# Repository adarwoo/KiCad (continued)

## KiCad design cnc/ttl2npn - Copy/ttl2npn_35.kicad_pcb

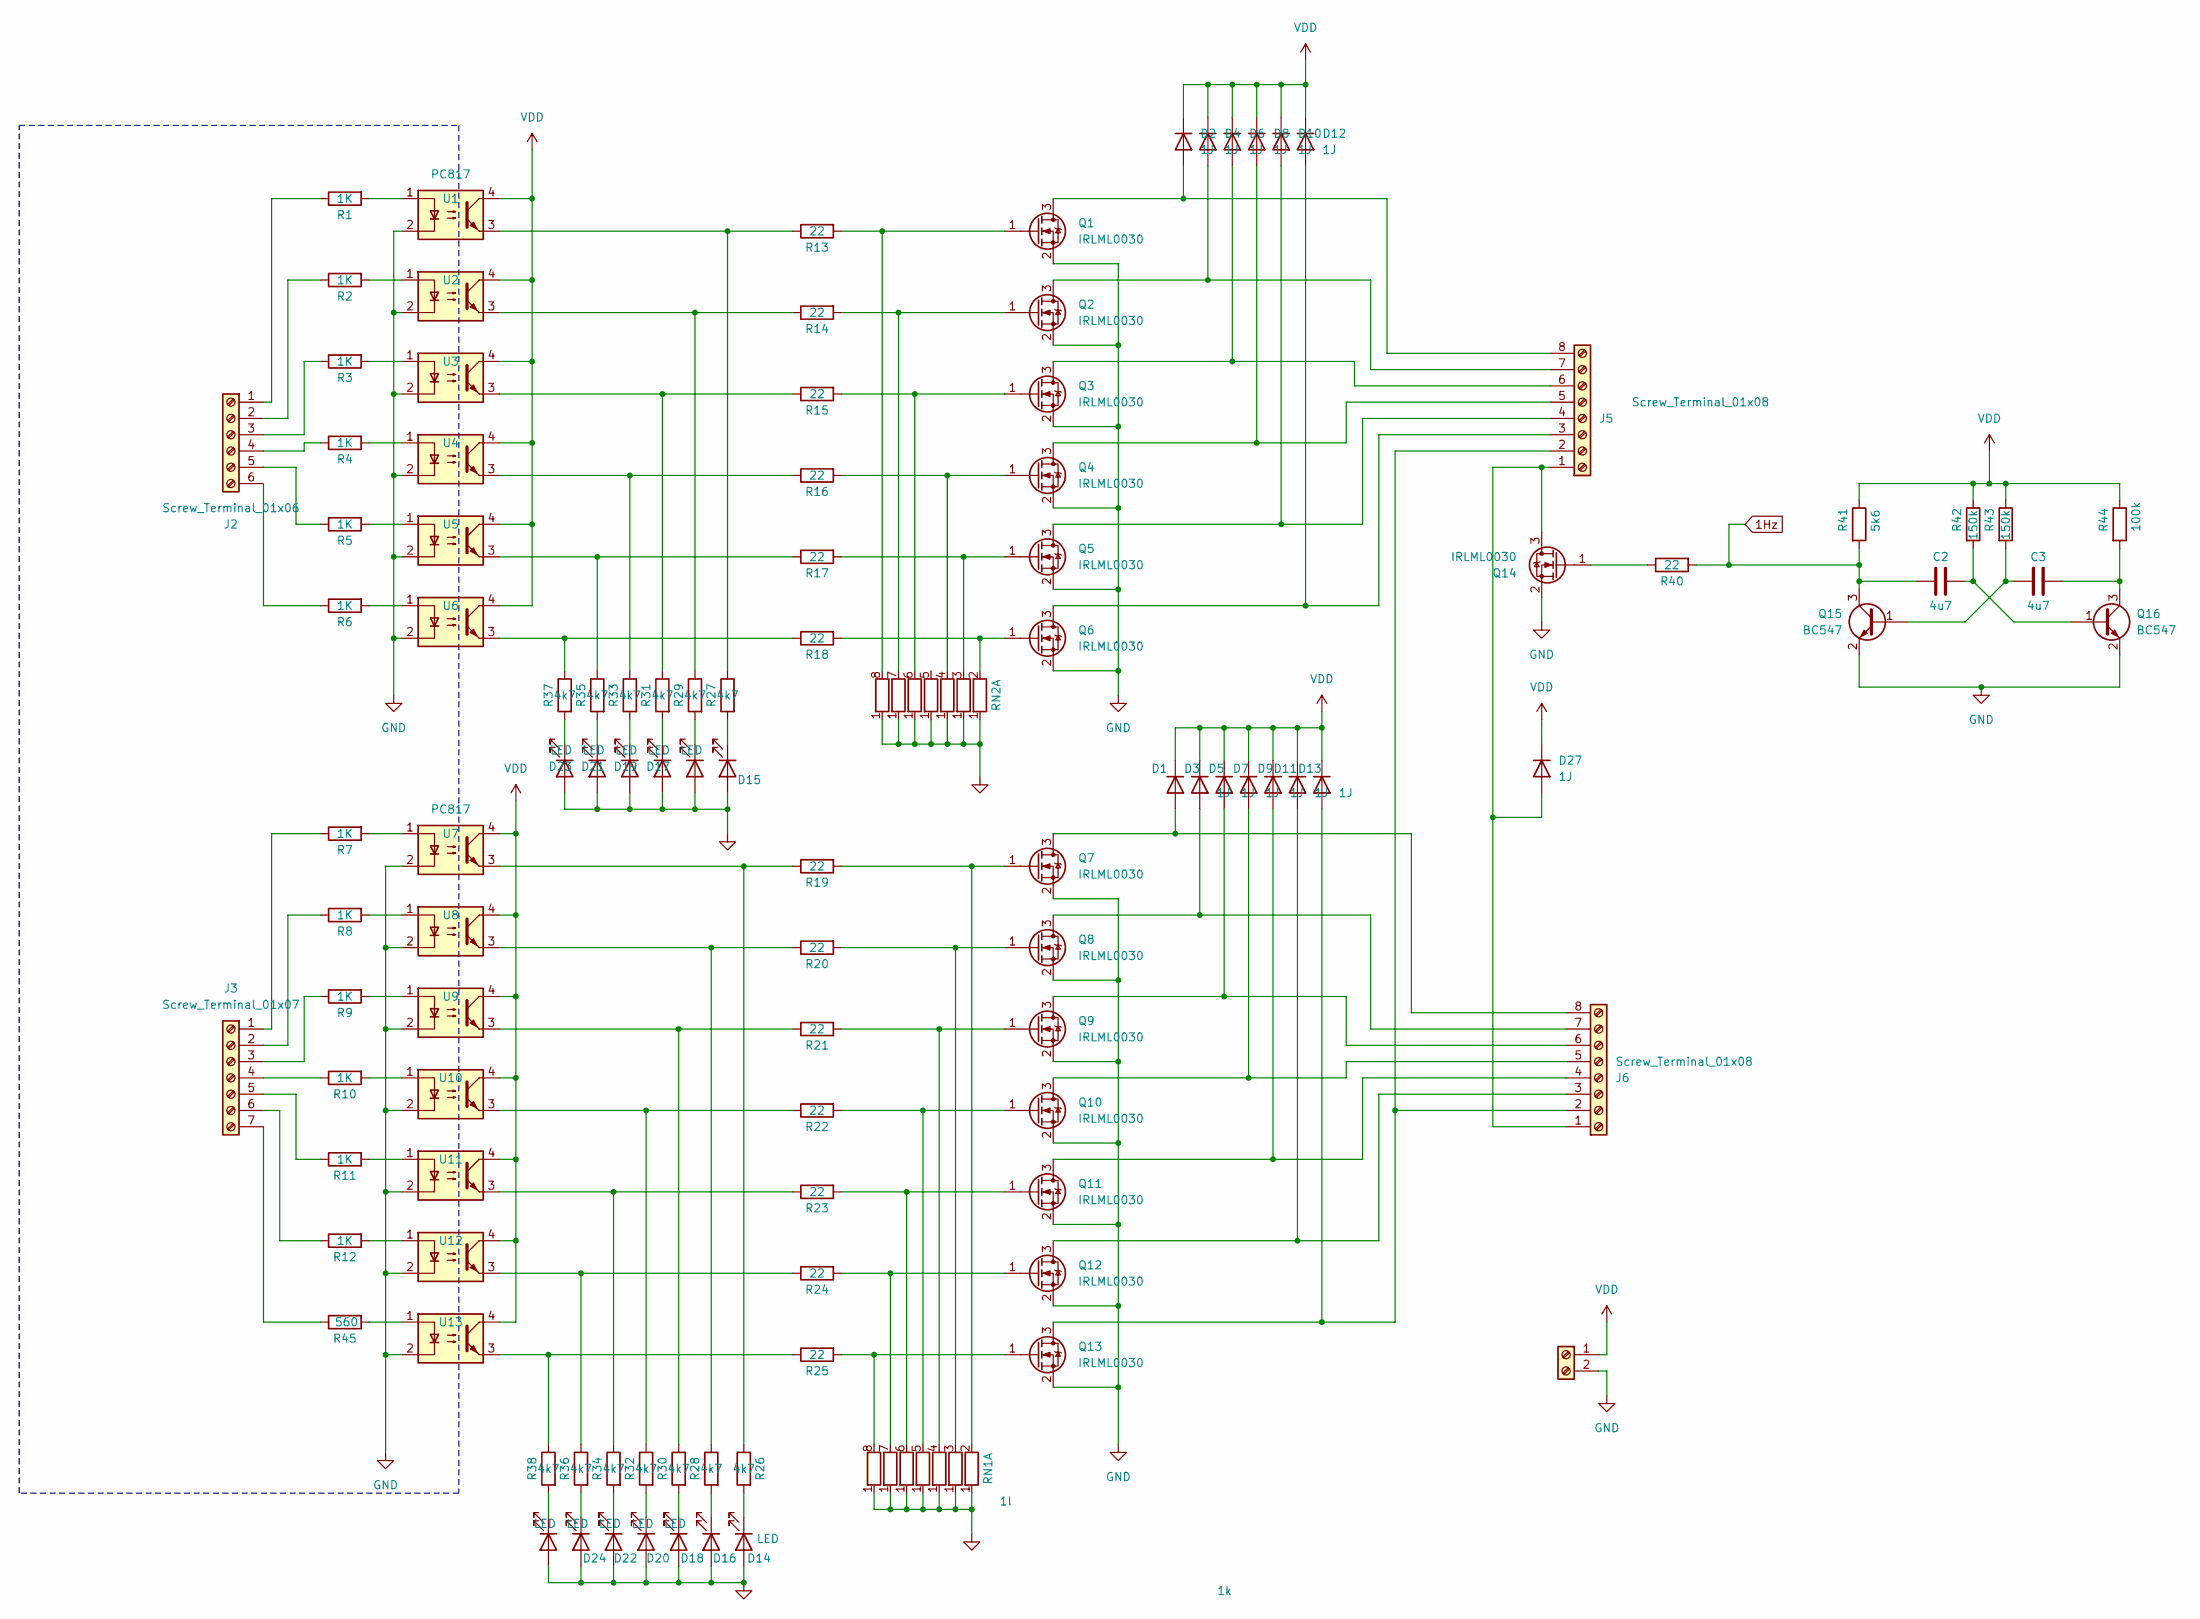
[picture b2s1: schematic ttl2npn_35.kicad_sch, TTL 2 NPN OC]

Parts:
C2, C3: 4u7; C_1206_3216Metric
D1, D2, D3, D4, D5, D6, D7, D8, D9, D10, D11, D12, D13, D27: 1J; D_MicroSMP_AK
D14, D15, D16, D17, D18, D19, D20, D21, D22, D23, D24, D25, D26: LED; LED_D3.0mm
J2: Screw_Terminal_01x06; PhoenixContact_MCV_1,5_6-G-3.81_1x06_P3.81mm_Vertical
J3: Screw_Terminal_01x07; PhoenixContact_MCV_1,5_7-G-3.81_1x07_P3.81mm_Vertical
J4: Screw_Terminal_01x02; PhoenixContact_MCV_1,5_2-G-3.81_1x02_P3.81mm_Vertical
J5, J6: Screw_Terminal_01x08; PhoenixContact_MCV_1,5_8-G-3.81_1x08_P3.81mm_Vertical
Q1, Q2, Q3, Q4, Q5, Q6, Q7, Q8, Q9, Q10, Q11, Q12, Q13, Q14: IRLML0030; SOT-23
Q15, Q16: BC547; SOT-23
R1, R2, R3, R4, R5, R6, R7, R8, R9, R10, R11, R12: 1K; R_0805_2012Metric
R13, R14, R15, R16, R17, R18, R19, R20, R21, R22, R23, R24, R25, R40: 22; R_0805_2012Metric
R26, R27, R28, R29, R30, R31, R32, R33, R34, R35, R36, R37, R38: 4k7; R_0805_2012Metric
R41: 5k6; R_0805_2012Metric
R42, R43: 150k; R_0805_2012Metric
R44: 100k; R_0805_2012Metric
R45: 560; R_0805_2012Metric
RN1: 1l; R_Array_SIP8
RN2: 1k; R_Array_SIP8
U1, U2, U3, U4, U5, U6, U7, U8, U9, U10, U11, U12, U13: PC817; DIP-4_W7.62mm

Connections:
1Hz: C2.1, Q15.3 (C), R40.2, R41.2
GND: D14.2 (A), D15.2 (A), D16.2 (A), D17.2 (A), D18.2 (A), D19.2 (A), D20.2 (A), D21.2 (A), D22.2 (A), D23.2 (A), D24.2 (A), D25.2 (A), D26.2 (A), J4.2, Q1.2 (S), Q2.2 (S), Q3.2 (S), Q4.2 (S), Q5.2 (S), Q6.2 (S), Q7.2 (S), Q8.2 (S), Q9.2 (S), Q10.2 (S), Q11.2 (S), Q12.2 (S), Q13.2 (S), Q14.2 (S), Q15.2 (E), Q16.2 (E), RN1.1 (R1), RN2.1 (R1), U1.2, U2.2, U3.2, U4.2, U5.2, U6.2, U7.2, U8.2, U9.2, U10.2, U11.2, U12.2, U13.2
unnamed: D1.2 (A), J6.8, Q7.3 (D)
unnamed: D2.2 (A), J5.8, Q1.3 (D)
unnamed: D3.2 (A), J6.7, Q8.3 (D)
unnamed: D4.2 (A), J5.7, Q2.3 (D)
unnamed: D5.2 (A), J6.6, Q9.3 (D)
unnamed: D6.2 (A), J5.6, Q3.3 (D)
unnamed: D7.2 (A), J6.5, Q10.3 (D)
unnamed: D8.2 (A), J5.5, Q4.3 (D)
unnamed: D9.2 (A), J6.4, Q11.3 (D)
unnamed: D10.2 (A), J5.4, Q5.3 (D)
unnamed: D11.2 (A), J6.3, Q12.3 (D)
unnamed: D12.2 (A), J5.3, Q6.3 (D)
unnamed: D13.2 (A), J5.2, J6.2, Q13.3 (D)
unnamed: D14.1 (K), R26.2
unnamed: D15.1 (K), R27.2
unnamed: D16.1 (K), R28.2
unnamed: D17.1 (K), R29.2
unnamed: D18.1 (K), R30.2
unnamed: D19.1 (K), R31.2
unnamed: D20.1 (K), R32.2
unnamed: D21.1 (K), R33.2
unnamed: D22.1 (K), R34.2
unnamed: D23.1 (K), R35.2
unnamed: D24.1 (K), R36.2
unnamed: D25.1 (K), R37.2
unnamed: D26.1 (K), R38.2
unnamed: D27.2 (A), J5.1, J6.1, Q14.3 (D)
unnamed: J2.1, R1.1
unnamed: J2.2, R2.1
unnamed: J2.3, R3.1
unnamed: J2.4, R4.1
unnamed: J2.5, R5.1
unnamed: J2.6, R6.1
unnamed: J3.1, R7.1
unnamed: J3.2, R8.1
unnamed: J3.3, R9.1
unnamed: J3.4, R10.1
unnamed: J3.5, R11.1
unnamed: J3.6, R12.1
unnamed: J3.7, R45.1
unnamed: Q1.1 (G), R13.2, RN2.8 (R7.2)
unnamed: Q2.1 (G), R14.2, RN2.7 (R6.2)
unnamed: Q3.1 (G), R15.2, RN2.6 (R5.2)
unnamed: Q4.1 (G), R16.2, RN2.4 (R3.2)
unnamed: Q5.1 (G), R17.2, RN2.3 (R2.2)
unnamed: Q6.1 (G), R18.2, RN2.2 (R1.2)
unnamed: Q7.1 (G), R19.2, RN1.2 (R1.2)
unnamed: Q8.1 (G), R20.2, RN1.3 (R2.2)
unnamed: Q9.1 (G), R21.2, RN1.4 (R3.2)
unnamed: Q10.1 (G), R22.2, RN1.5 (R4.2)
unnamed: Q11.1 (G), R23.2, RN1.6 (R5.2)
unnamed: Q12.1 (G), R24.2, RN1.7 (R6.2)
unnamed: Q13.1 (G), R25.2, RN1.8 (R7.2)
unnamed: Q14.1 (G), R40.1
unnamed: C3.1, Q15.1 (B), R43.2
unnamed: C2.2, Q16.1 (B), R42.2
unnamed: C3.2, Q16.3 (C), R44.2
unnamed: R1.2, U1.1
unnamed: R2.2, U2.1
unnamed: R3.2, U3.1
unnamed: R4.2, U4.1
unnamed: R5.2, U5.1
unnamed: R6.2, U6.1
unnamed: R7.2, U7.1
unnamed: R8.2, U8.1
unnamed: R9.2, U9.1
unnamed: R10.2, U10.1
unnamed: R11.2, U11.1
unnamed: R12.2, U12.1
unnamed: R13.1, R27.1, U1.3
unnamed: R14.1, R29.1, U2.3
unnamed: R15.1, R31.1, U3.3
unnamed: R16.1, R33.1, U4.3
unnamed: R17.1, R35.1, U5.3
unnamed: R18.1, R37.1, U6.3
unnamed: R19.1, R26.1, U7.3
unnamed: R20.1, R28.1, U8.3
unnamed: R21.1, R30.1, U9.3
unnamed: R22.1, R32.1, U10.3
unnamed: R23.1, R34.1, U11.3
unnamed: R24.1, R36.1, U12.3
unnamed: R25.1, R38.1, U13.3
unnamed: R45.2, U13.1
VDD: D1.1 (K), D2.1 (K), D3.1 (K), D4.1 (K), D5.1 (K), D6.1 (K), D7.1 (K), D8.1 (K), D9.1 (K), D10.1 (K), D11.1 (K), D12.1 (K), D13.1 (K), D27.1 (K), J4.1, R41.1, R42.1, R43.1, R44.1, U1.4, U2.4, U3.4, U4.4, U5.4, U6.4, U7.4, U8.4, U9.4, U10.4, U11.4, U12.4, U13.4

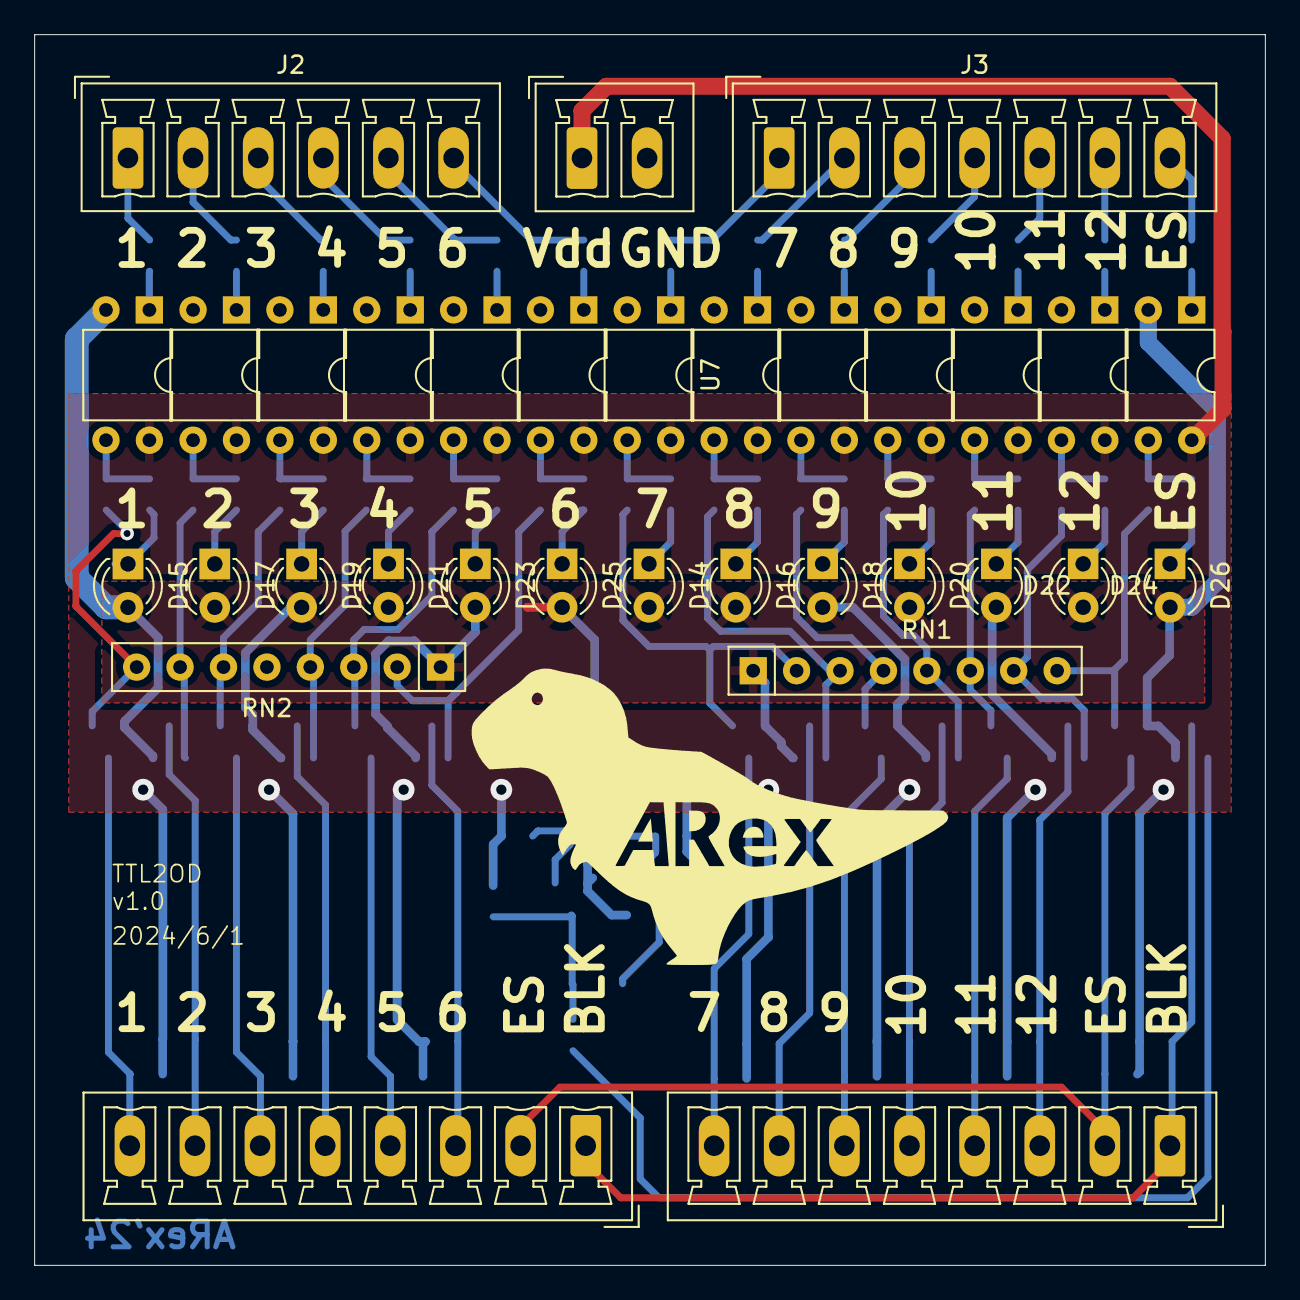
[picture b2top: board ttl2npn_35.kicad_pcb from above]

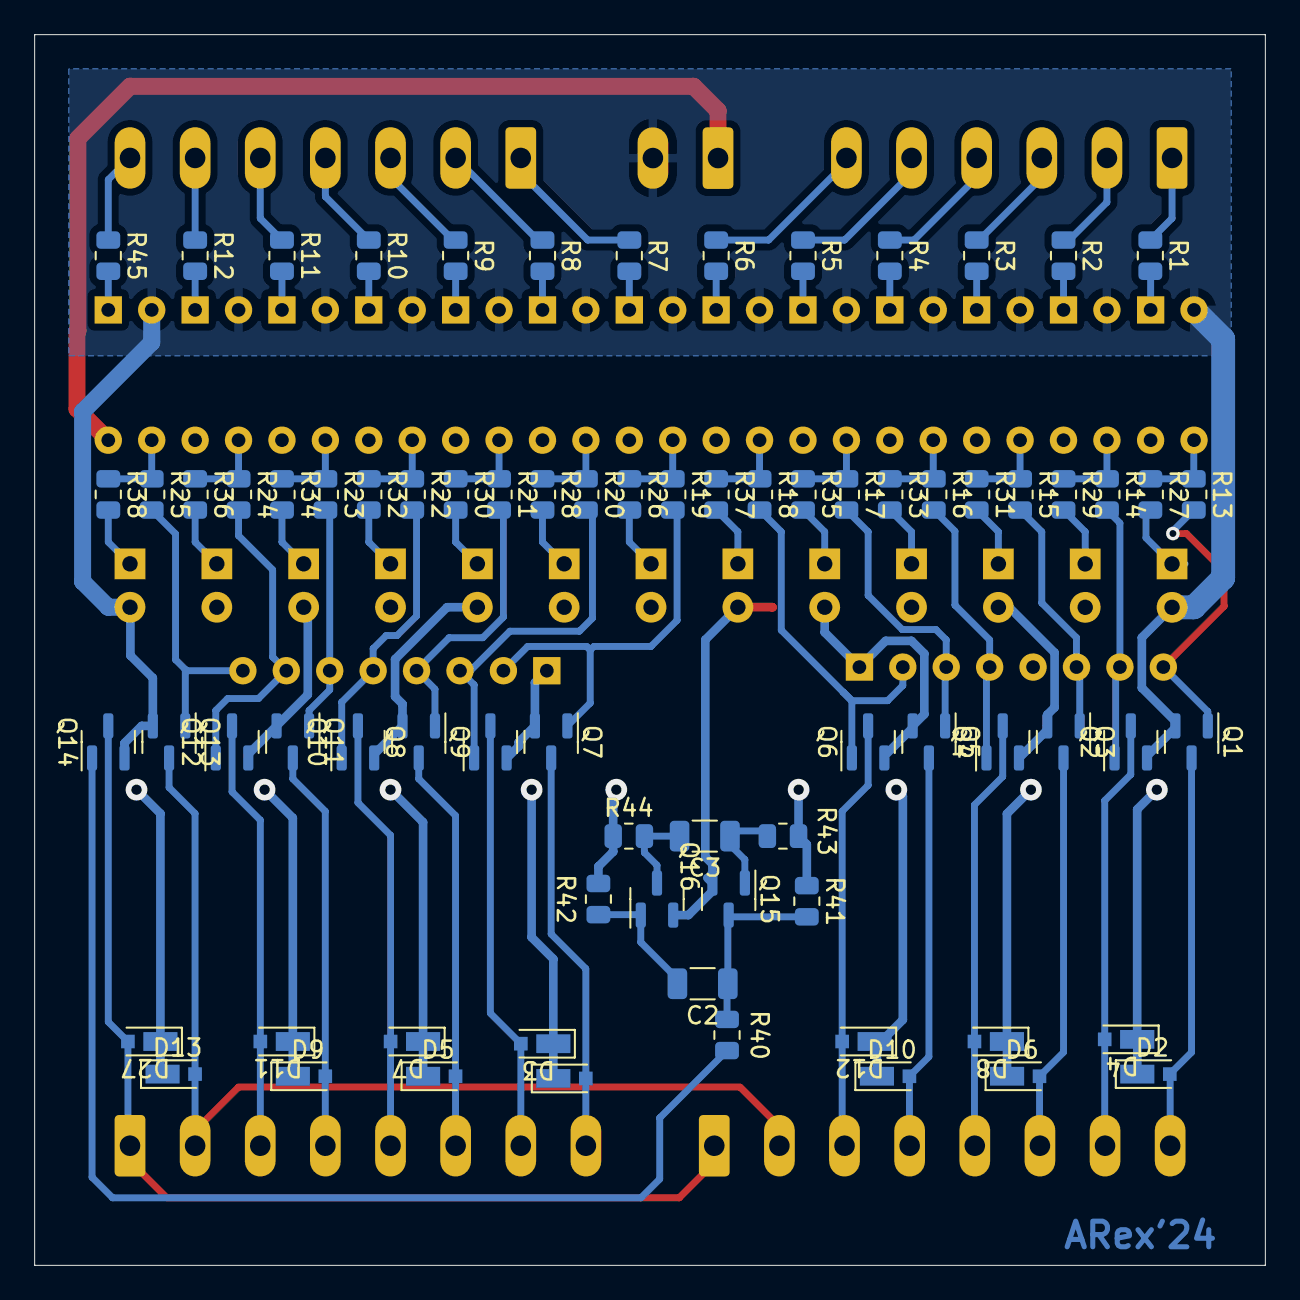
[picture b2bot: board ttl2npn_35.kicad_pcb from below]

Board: 2 copper layers, 72.0 x 72.0 mm, 109 parts (76 on the bottom side), 86 nets.

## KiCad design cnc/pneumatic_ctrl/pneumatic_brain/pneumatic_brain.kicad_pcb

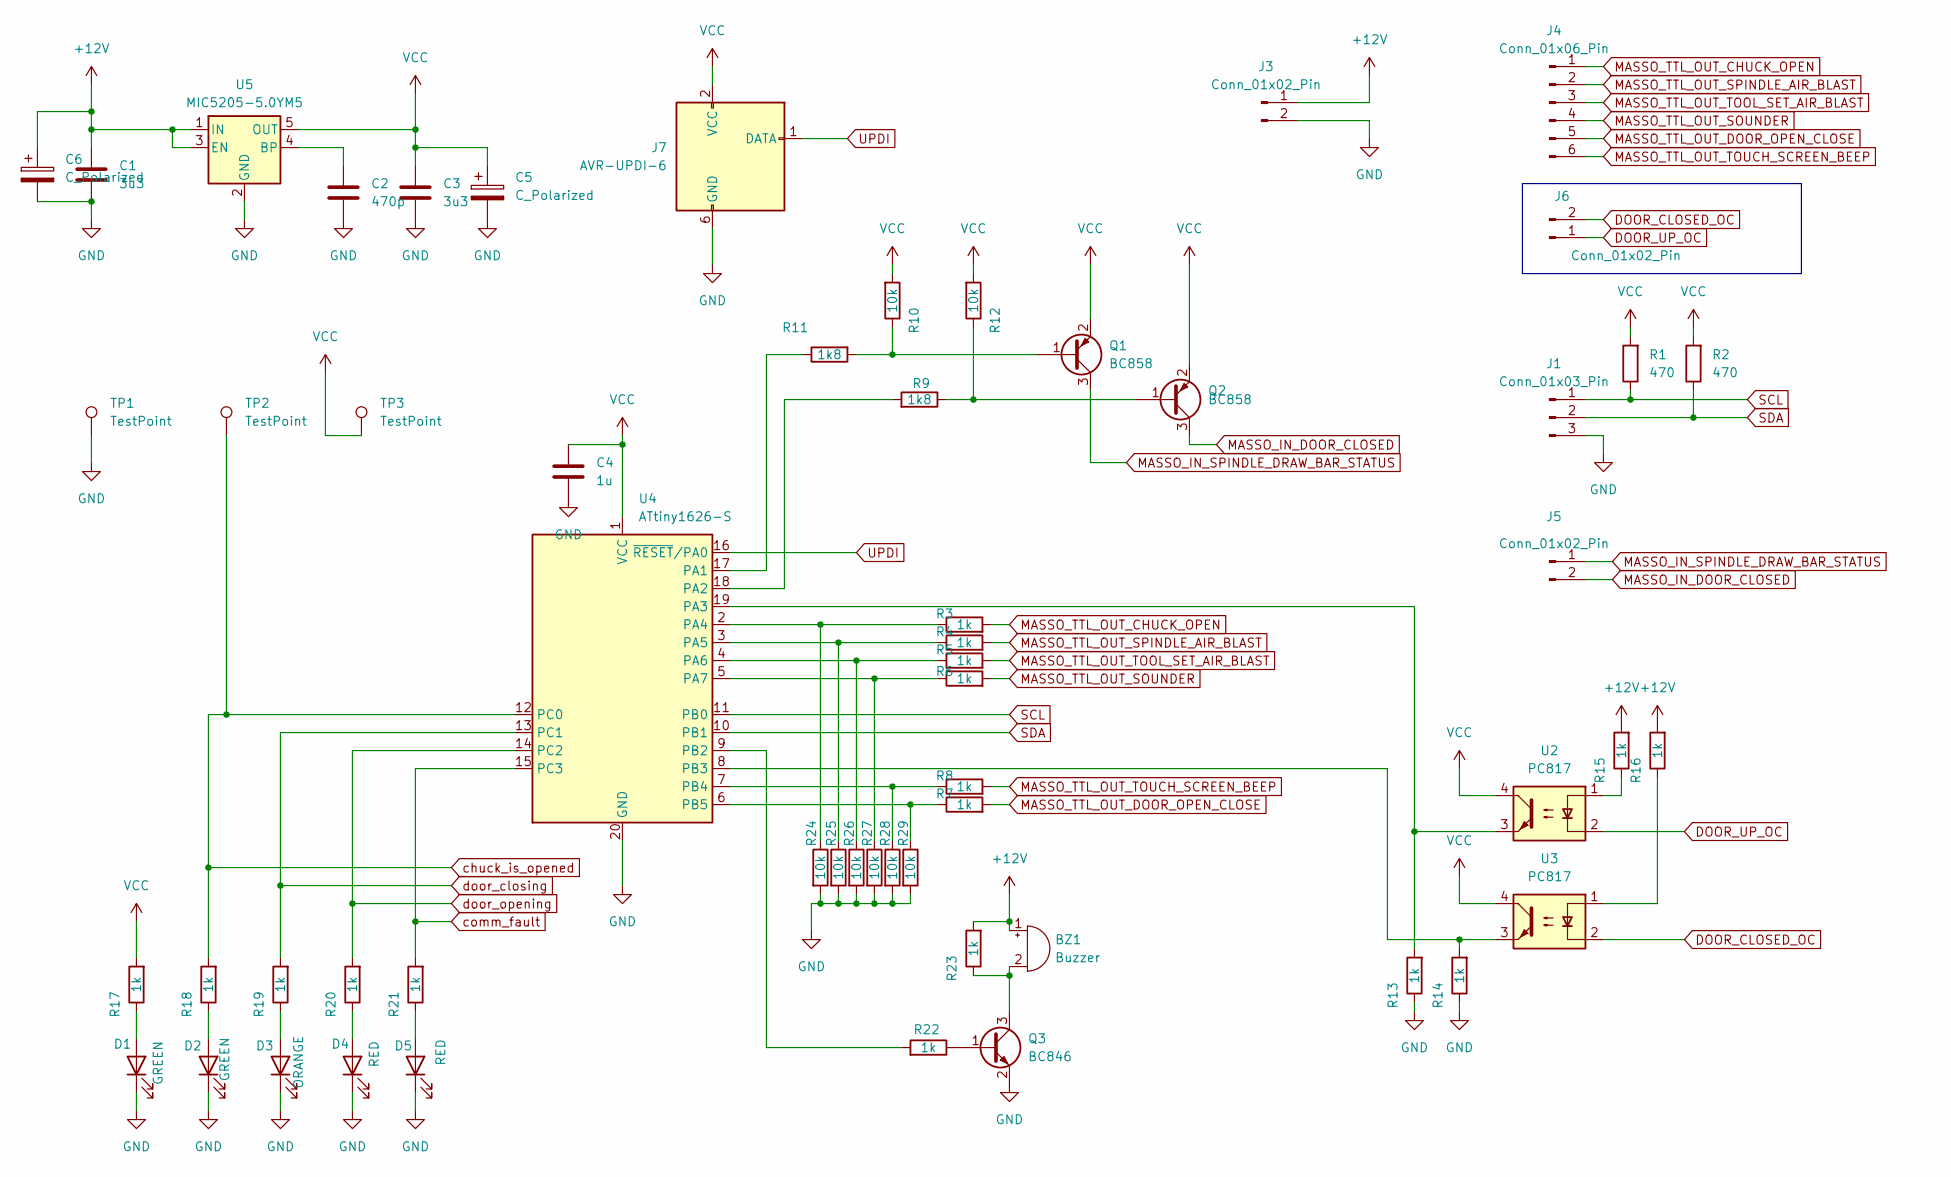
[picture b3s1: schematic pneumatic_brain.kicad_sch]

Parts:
BZ1: Buzzer; Buzzer_15x7.5RM7.6
C1, C3: 3u3; C_1206_3216Metric_Pad1.33x1.80mm_HandSolder
C2: 470p; C_0805_2012Metric_Pad1.18x1.45mm_HandSolder
C4: 1u; C_0805_2012Metric_Pad1.18x1.45mm_HandSolder
C5, C6: C_Polarized; C_1210_3225Metric_Pad1.33x2.70mm_HandSolder
D1, D2: GREEN; LED_D3.0mm
D3: ORANGE; LED_D3.0mm
D4, D5: RED; LED_D3.0mm
J1: Conn_01x03_Pin; PhoenixContact_MCV_1,5_3-G-3.81_1x03_P3.81mm_Vertical
J3, J5, J6: Conn_01x02_Pin; PhoenixContact_MCV_1,5_2-G-3.81_1x02_P3.81mm_Vertical
J4: Conn_01x06_Pin; PhoenixContact_MCV_1,5_6-G-3.81_1x06_P3.81mm_Vertical
J7: AVR-UPDI-6; PinHeader_2x03_P2.54mm_Vertical
Q1, Q2: BC858; SOT-23
Q3: BC846; SOT-23
R1, R2: 470; R_1206_3216Metric_Pad1.30x1.75mm_HandSolder
R3, R4, R5, R6, R7, R8, R13, R14, R15, R16, R17, R18, R19, R20, R21, R22, R23: 1k; R_1206_3216Metric_Pad1.30x1.75mm_HandSolder
R9, R11: 1k8; R_1206_3216Metric_Pad1.30x1.75mm_HandSolder
R10, R12, R24, R25, R26, R27, R28, R29: 10k; R_1206_3216Metric_Pad1.30x1.75mm_HandSolder
TP1, TP2, TP3: TestPoint; TestPoint_Loop_D2.60mm_Drill1.6mm_Beaded
U2, U3: PC817; DIP-4_W7.62mm
U4: ATtiny1626-S; SOIC-20W_7.5x12.8mm_P1.27mm
U5: MIC5205-5.0YM5; SOT-23-5

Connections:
+12V: BZ1.1 (+), C1.1, C6.1, J3.1, R15.2, R16.2, R23.2, U5.1 (IN), U5.3 (EN)
DOOR_CLOSED_OC: J6.2, U3.2
DOOR_UP_OC: J6.1, U2.2
GND: C1.2, C2.2, C3.2, C4.2, C5.2, C6.2, D1.1 (K), D2.1 (K), D3.1 (K), D4.1 (K), D5.1 (K), J1.3, J3.2, J7.6 (GND), Q3.2 (E), R13.1, R14.1, R24.2, R25.2, R26.2, R27.2, R28.2, R29.2, TP1.1, U4.20 (GND), U5.2 (GND)
MASSO_IN_DOOR_CLOSED: J5.2, Q2.3 (C)
MASSO_IN_SPINDLE_DRAW_BAR_STATUS: J5.1, Q1.3 (C)
MASSO_TTL_OUT_CHUCK_OPEN: J4.1, R3.2
MASSO_TTL_OUT_DOOR_OPEN_CLOSE: J4.5, R7.2
MASSO_TTL_OUT_SOUNDER: J4.4, R6.2
MASSO_TTL_OUT_SPINDLE_AIR_BLAST: J4.2, R4.2
MASSO_TTL_OUT_TOOL_SET_AIR_BLAST: J4.3, R5.2
MASSO_TTL_OUT_TOUCH_SCREEN_BEEP: J4.6, R8.2
unnamed: BZ1.2 (-), Q3.3 (C), R23.1
unnamed: D1.2 (A), R17.1
unnamed: D2.2 (A), R18.1
unnamed: D3.2 (A), R19.1
unnamed: D4.2 (A), R20.1
unnamed: D5.2 (A), R21.1
unnamed: Q1.1 (B), R10.1, R11.2
unnamed: Q2.1 (B), R9.1, R12.1
unnamed: Q3.1 (B), R22.1
unnamed: R15.1, U2.1
unnamed: R16.1, U3.1
unnamed: R11.1, U4.17 (PA1)
unnamed: R9.2, U4.18 (PA2)
unnamed: R13.2, U2.3, U4.19 (PA3)
unnamed: R3.1, R24.1, U4.2 (PA4)
unnamed: R4.1, R25.1, U4.3 (PA5)
unnamed: R5.1, R26.1, U4.4 (PA6)
unnamed: R6.1, R27.1, U4.5 (PA7)
unnamed: R22.2, U4.9 (PB2)
unnamed: R14.2, U3.3, U4.8 (PB3)
unnamed: R8.1, R28.1, U4.7 (PB4)
unnamed: R7.1, R29.1, U4.6 (PB5)
unnamed: C2.1, U5.4 (BP)
SCL: J1.1, R1.1, U4.11 (PB0)
SDA: J1.2, R2.1, U4.10 (PB1)
UPDI: J7.1 (DATA), U4.16 (~RESET/PA0)
VCC: C3.1, C4.1, C5.1, J7.2 (VCC), Q1.2 (E), Q2.2 (E), R1.2, R2.2, R10.2, R12.2, R17.2, TP3.1, U2.4, U3.4, U4.1 (VCC), U5.5 (OUT)
chuck_is_opened: R18.2, TP2.1, U4.12 (PC0)
comm_fault: R21.2, U4.15 (PC3)
door_closing: R19.2, U4.13 (PC1)
door_opening: R20.2, U4.14 (PC2)

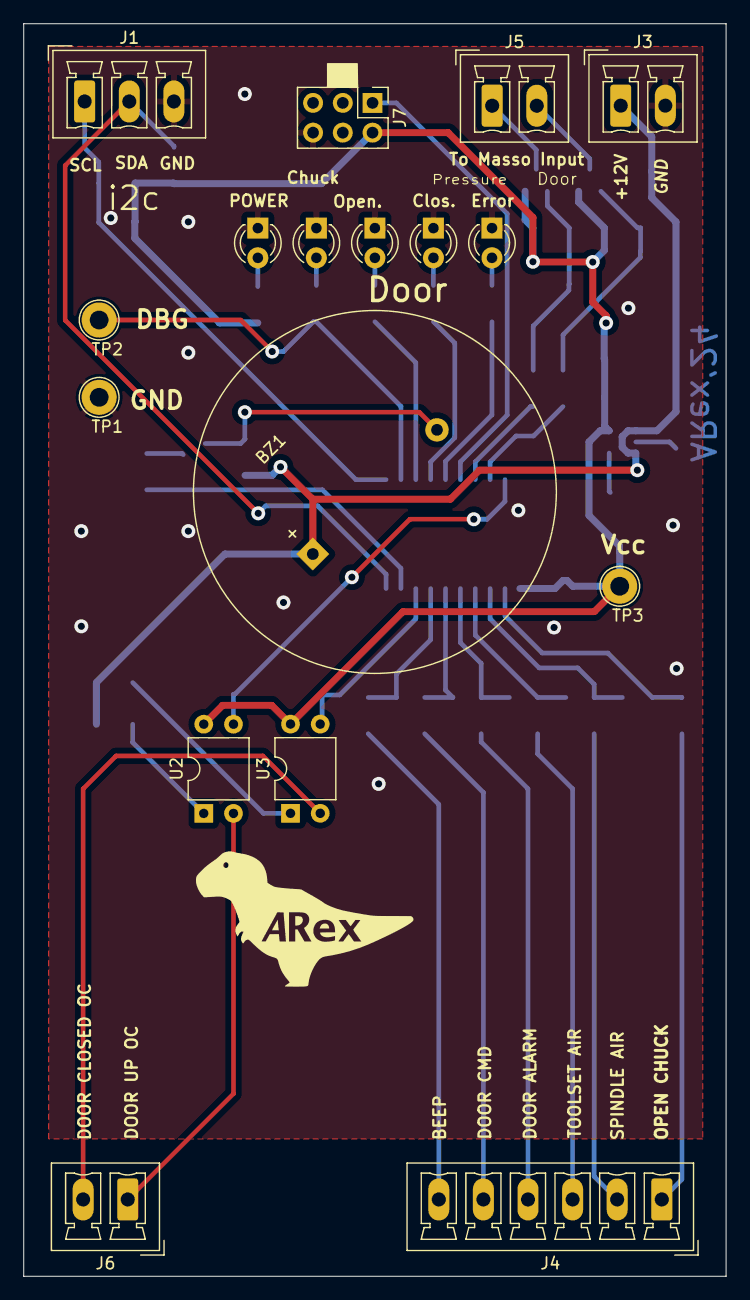
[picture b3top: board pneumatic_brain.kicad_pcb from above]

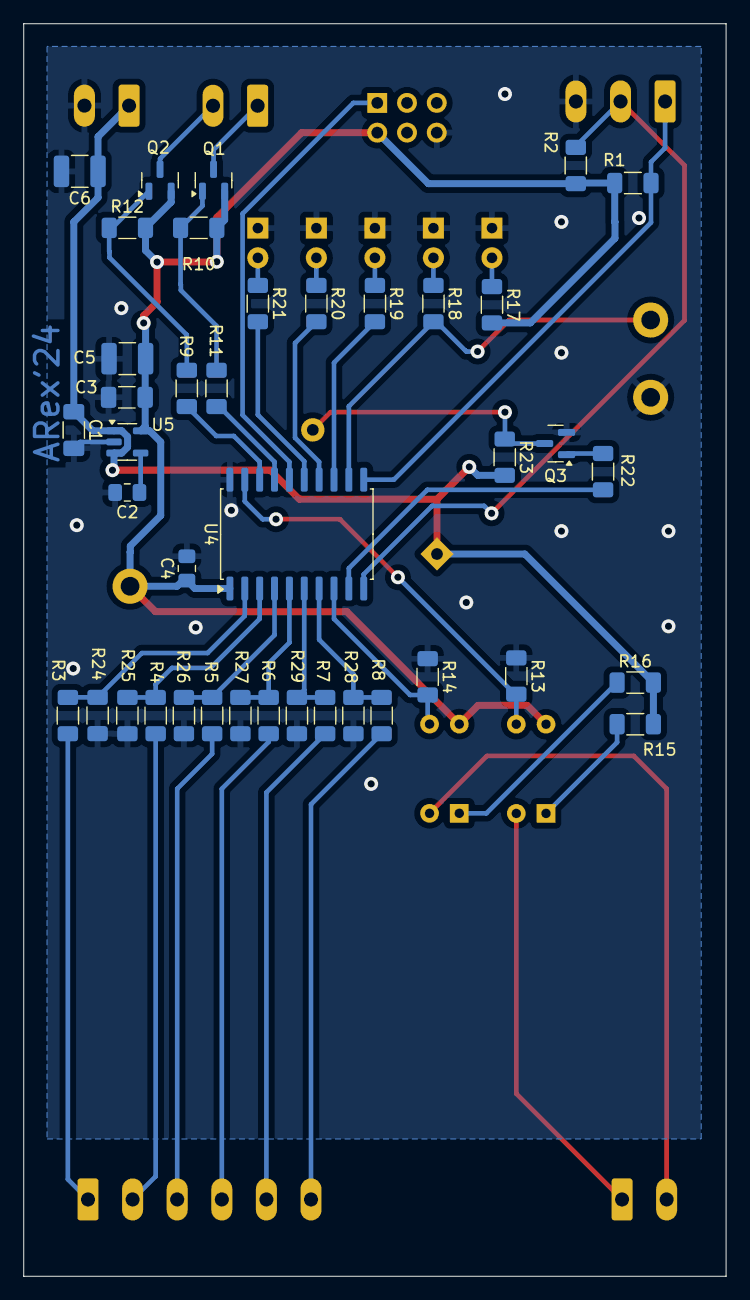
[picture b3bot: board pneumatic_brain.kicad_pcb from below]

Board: 2 copper layers, 60.0 x 107.0 mm, 57 parts (40 on the bottom side), 43 nets.

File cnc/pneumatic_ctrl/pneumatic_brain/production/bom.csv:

Designator,Footprint,Quantity,Value,LCSC Part #
BZ1,Buzzer_15x7.5RM7.6,1,Buzzer,
"C1, C3",1206,2,3u3,
C2,0805,1,470p,
C4,0805,1,1u,
"C5, C6",1210,2,C_Polarized,
"D1, D2",LED_D3.0mm,2,GREEN,
D3,LED_D3.0mm,1,ORANGE,
"D4, D5",LED_D3.0mm,2,RED,
J1,"PhoenixContact_MCV_1,5_3-G-3.81_1x03_P3.81mm_Vertical",1,Conn_01x03_Pin,
"J3, J5, J6","PhoenixContact_MCV_1,5_2-G-3.81_1x02_P3.81mm_Vertical",3,Conn_01x02_Pin,
J4,"PhoenixContact_MCV_1,5_6-G-3.81_1x06_P3.81mm_Vertical",1,Conn_01x06_Pin,
J7,PinHeader_2x03_P2.54mm_Vertical,1,AVR-UPDI-6,
"Q1, Q2",SOT-23,2,BC858,
Q3,SOT-23,1,BC846,
"R1, R2",1206,2,470,
"R10, R12, R24, R25, R26, R27, R28, R29",1206,8,10k,
"R11, R9",1206,2,1k8,
"R13, R14, R15, R16, R17, R18, R19, R20, R21, R22, R23, R3, R4, R5, R6, R7, R8",1206,17,1k,
"TP1, TP2, TP3",TestPoint_Loop_D2.60mm_Drill1.6mm_Beaded,3,TestPoint,
"U2, U3",DIP-4_W7.62mm,2,PC817,
U4,SOIC-20W_7.5x12.8mm_P1.27mm,1,ATtiny3226-S,
U5,SOT-23-5,1,MIC5205-5.0YM5,

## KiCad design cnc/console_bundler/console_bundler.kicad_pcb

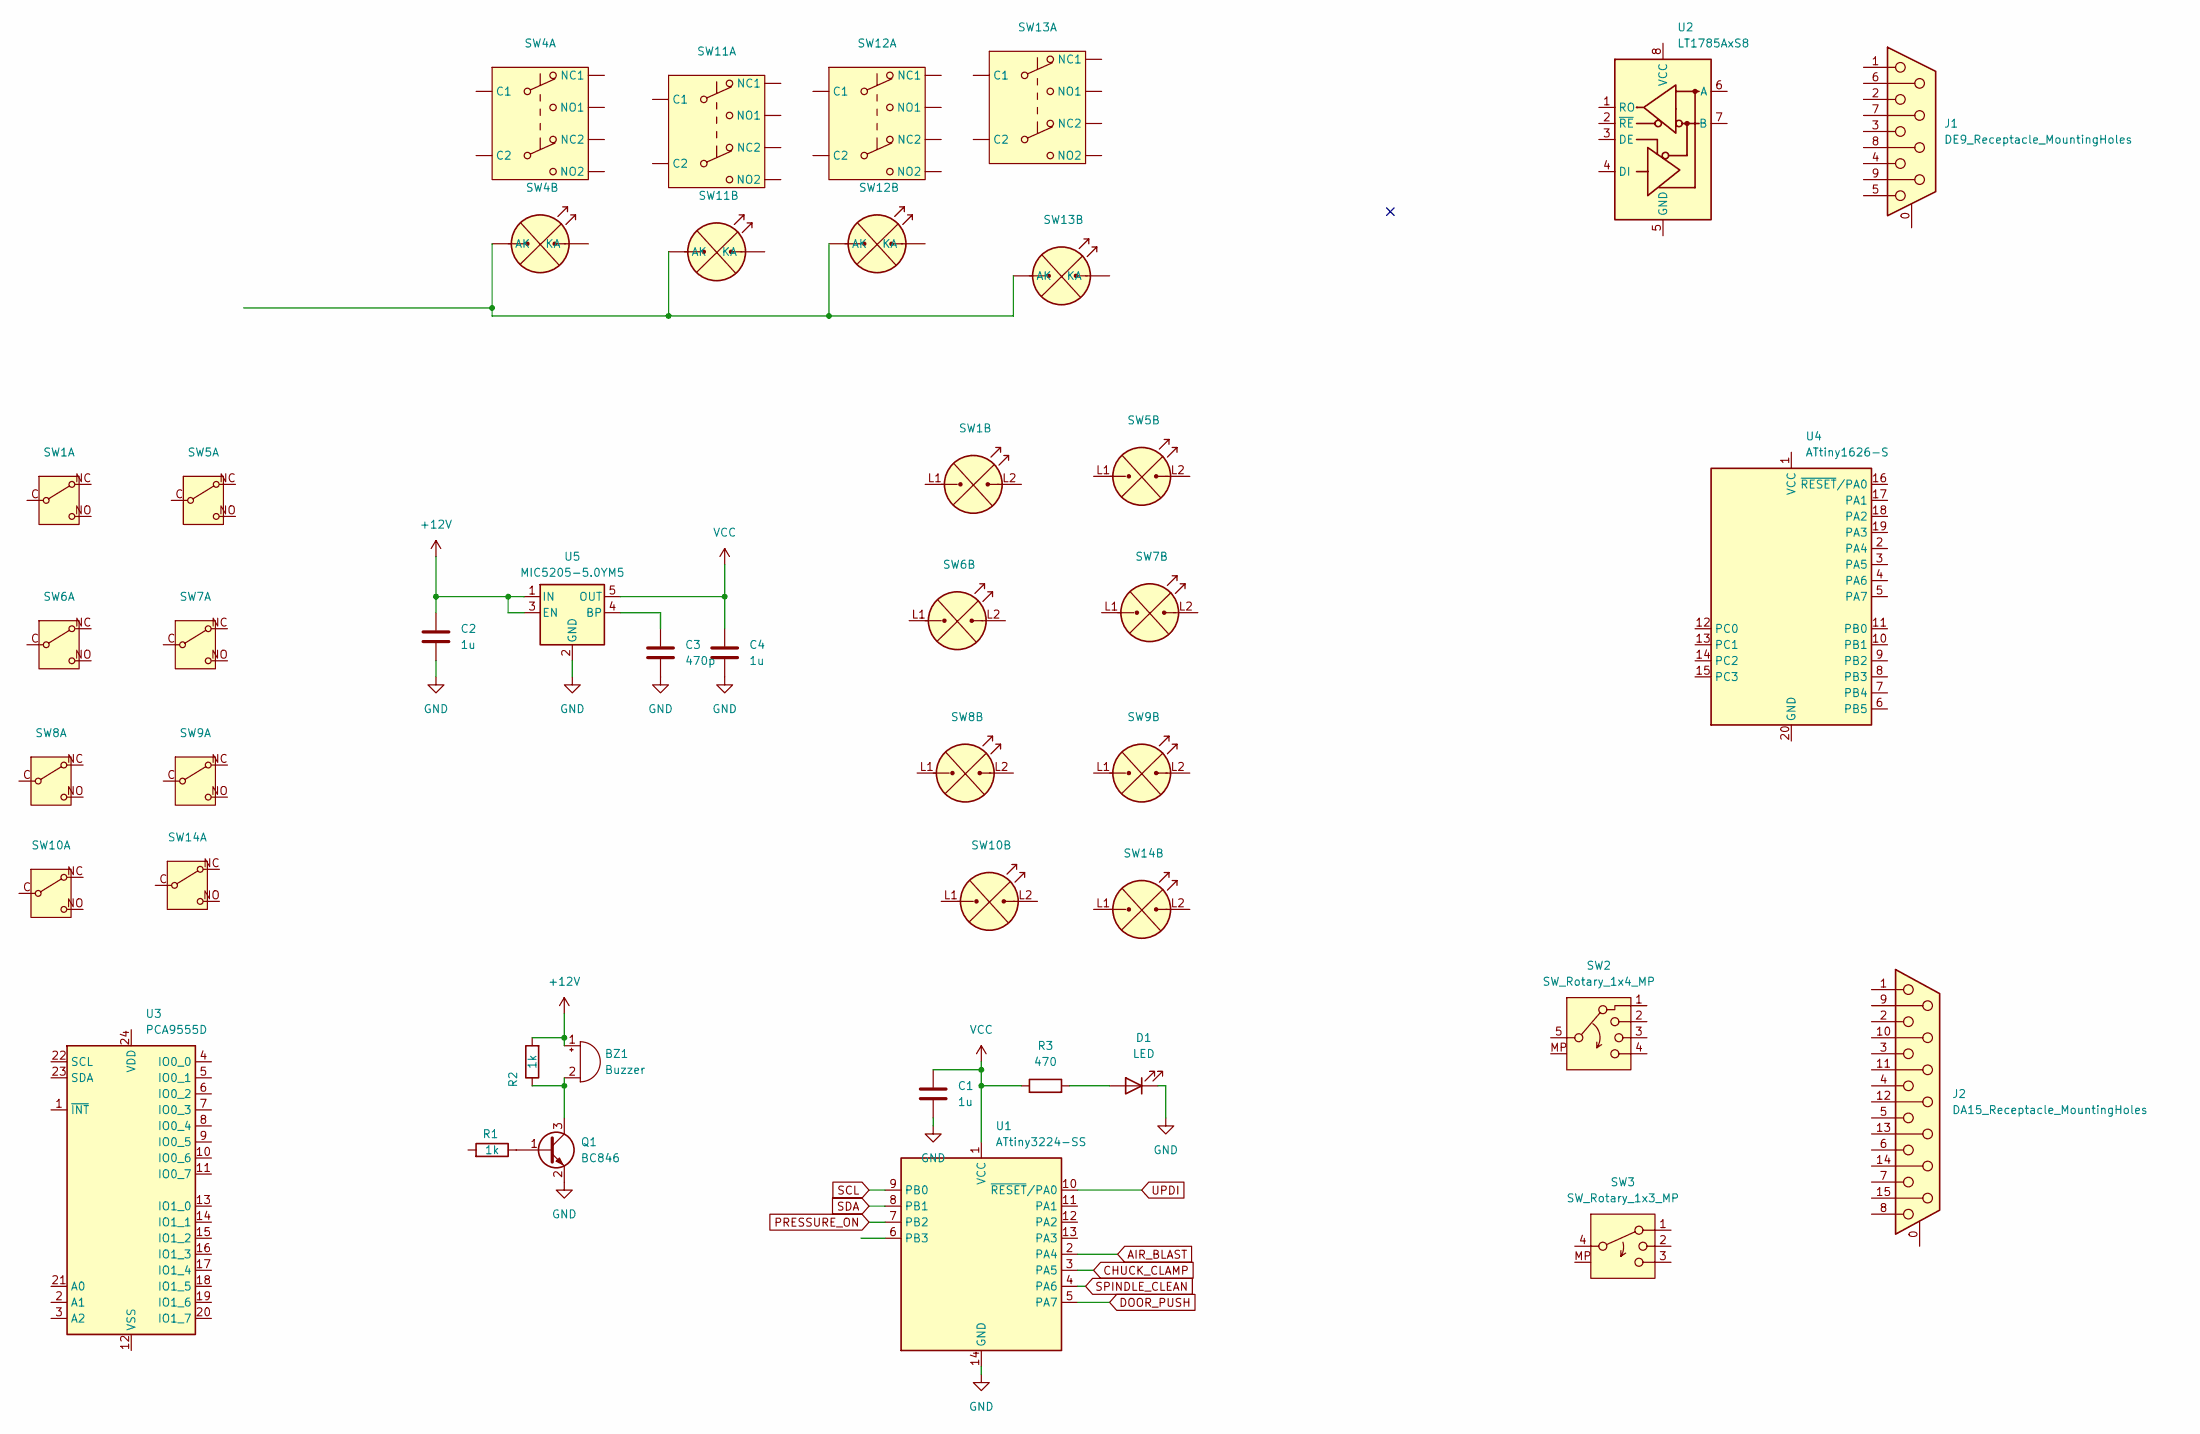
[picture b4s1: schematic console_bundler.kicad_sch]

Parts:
BZ1: Buzzer; Buzzer_15x7.5RM7.6
C1, C2, C4: 1u; C_1206_3216Metric_Pad1.33x1.80mm_HandSolder
C3: 470p; C_0805_2012Metric_Pad1.18x1.45mm_HandSolder
D1: LED; LED_D3.0mm
J1: DE9_Receptacle_MountingHoles; DSUB-9_Male_Horizontal_P2.77x2.84mm_EdgePinOffset4.94mm_Hou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
J2: DA15_Receptacle_MountingHoles; DSUB-15_Male_Horizontal_P2.77x2.84mm_EdgePinOffset7.70mm_Ho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
Q1: BC846; SOT-23
R1, R2: 1k; R_1206_3216Metric_Pad1.30x1.75mm_HandSolder
R3: 470; R_1206_3216Metric_Pad1.30x1.75mm_HandSolder
SW1, SW5, SW6, SW7, SW8, SW9, SW10, SW14: PUSH_STDP_LED
SW2: SW_Rotary_1x4_MP
SW3: SW_Rotary_1x3_MP
SW4, SW11, SW12, SW13: DPDT-LED12V
U1: ATtiny3224-SS; SOIC-14_3.9x8.7mm_P1.27mm
U2: LT1785AxS8; SOIC-8_3.9x4.9mm_P1.27mm
U3: PCA9555D; SOIC-24W_7.5x15.4mm_P1.27mm
U4: ATtiny1626-S; SOIC-20W_7.5x12.8mm_P1.27mm
U5: MIC5205-5.0YM5; SOT-23-5

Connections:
+12V: BZ1.1 (+), C2.1, R2.2, U5.1 (IN), U5.3 (EN)
AIR_BLAST: U1.2 (PA4)
CHUCK_CLAMP: U1.3 (PA5)
DOOR_PUSH: U1.5 (PA7)
GND: C1.2, C2.2, C3.2, C4.2, D1.1 (K), Q1.2 (E), U1.14 (GND), U5.2 (GND)
unnamed: BZ1.2 (-), Q1.3 (C), R2.1
unnamed: D1.2 (A), R3.2
unnamed: Q1.1 (B), R1.1
unnamed: SW4.L1 (AK), SW11.L1 (AK), SW12.L1 (AK), SW13.L1 (AK)
unnamed: C3.1, U5.4 (BP)
PRESSURE_ON: U1.7 (PB2)
SCL: U1.9 (PB0)
SDA: U1.8 (PB1)
SPINDLE_CLEAN: U1.4 (PA6)
UPDI: U1.10 (~RESET/PA0)
VCC: C1.1, C4.1, R3.1, U1.1 (VCC), U5.5 (OUT)

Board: 2 copper layers, 29 parts (0 on the bottom side), 8 nets, no tracks yet.

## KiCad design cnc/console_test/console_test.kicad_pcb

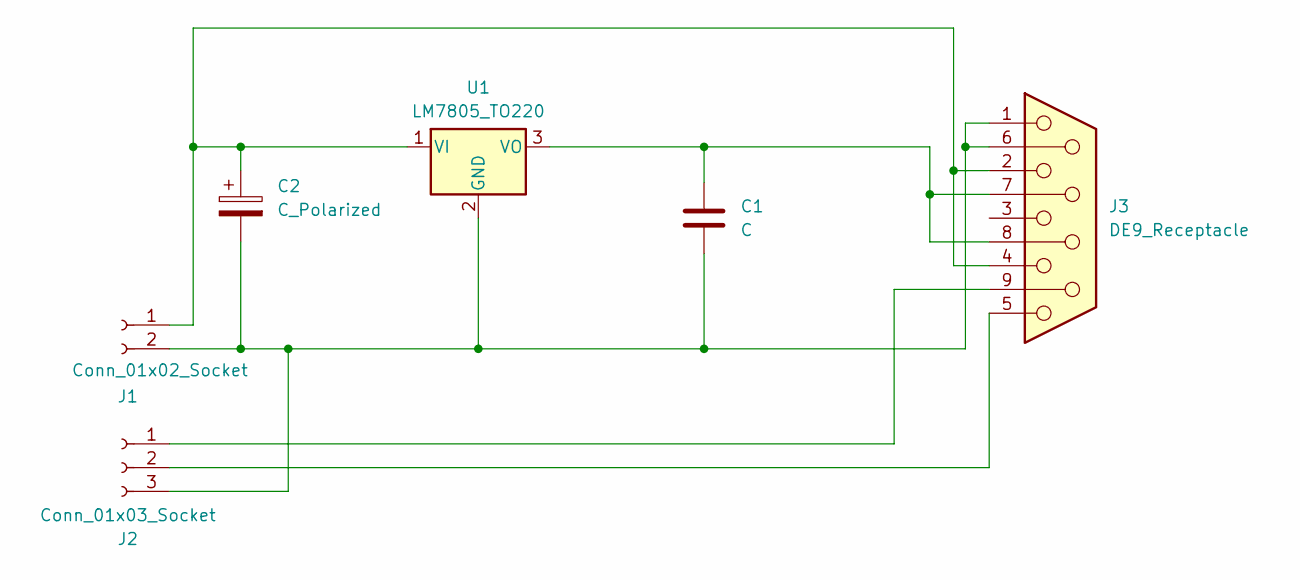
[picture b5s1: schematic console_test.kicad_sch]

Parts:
C1: C; C_Disc_D7.5mm_W4.4mm_P5.00mm
C2: C_Polarized; CP_Radial_Tantal_D5.0mm_P5.00mm
J1: Conn_01x02_Socket; PhoenixContact_MCV_1,5_2-G-3.81_1x02_P3.81mm_Vertical
J2: Conn_01x03_Socket; PhoenixContact_MCV_1,5_3-G-3.5_1x03_P3.50mm_Vertical
J3: DE9_Receptacle; DSUB-9_Female_Horizontal_P2.77x2.84mm_EdgePinOffset4.94mm_H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
U1: LM7805_TO220; TO-220-3_Vertical

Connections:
unnamed: C2.1, J1.1, J3.2, J3.4, U1.1 (VI)
unnamed: C1.2, C2.2, J1.2, J2.3, J3.1, J3.6, U1.2 (GND)
unnamed: J2.1, J3.9
unnamed: J2.2, J3.5
unnamed: C1.1, J3.7, J3.8, U1.3 (VO)

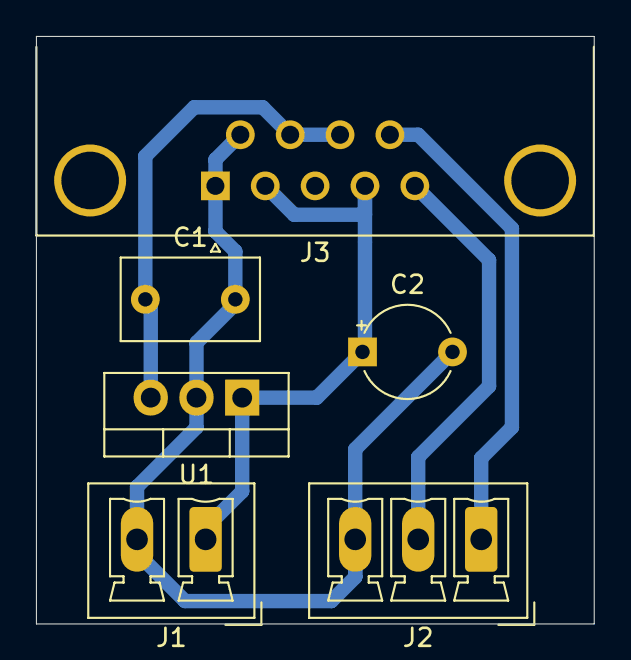
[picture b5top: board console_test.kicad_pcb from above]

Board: 2 copper layers, 31.0 x 32.6 mm, 6 parts (0 on the bottom side), 5 nets.
